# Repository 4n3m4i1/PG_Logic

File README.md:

# ProgrammaGull Logic
Small and open source FPGA development boards for all those still pecking for fries.  

## Hardware
Design files provided for KiCad 7.
  
### PGL Sandpiper
An education focused development platform, full of fun I/O and devices for users to learn the basics of real world FPGA development. The board centers around the Lattice iCE40-UP5k, which itself offers ample BRAM, PSRAM, 8 DSP Blocks, a PLL, and two internal oscillators.

### PGL E3
An iCE40-UP5k SG48 development board and associated programmer board.  
Designed to be embeddable and flexible enough for most projects!  
  
### PGL E6
A small embeddable Lattice iCE40-LP384 aimed at alleviating the overhead incurred when adding glue logic or general PL space into a project.

### PGL E6-NF
The same PGL E6 but with no flash, allowing smaller footprints when accompanied by some external bitstream source (MCU, external flash, other FPGA, etc..)

## Credits
Name: @slurpeecup

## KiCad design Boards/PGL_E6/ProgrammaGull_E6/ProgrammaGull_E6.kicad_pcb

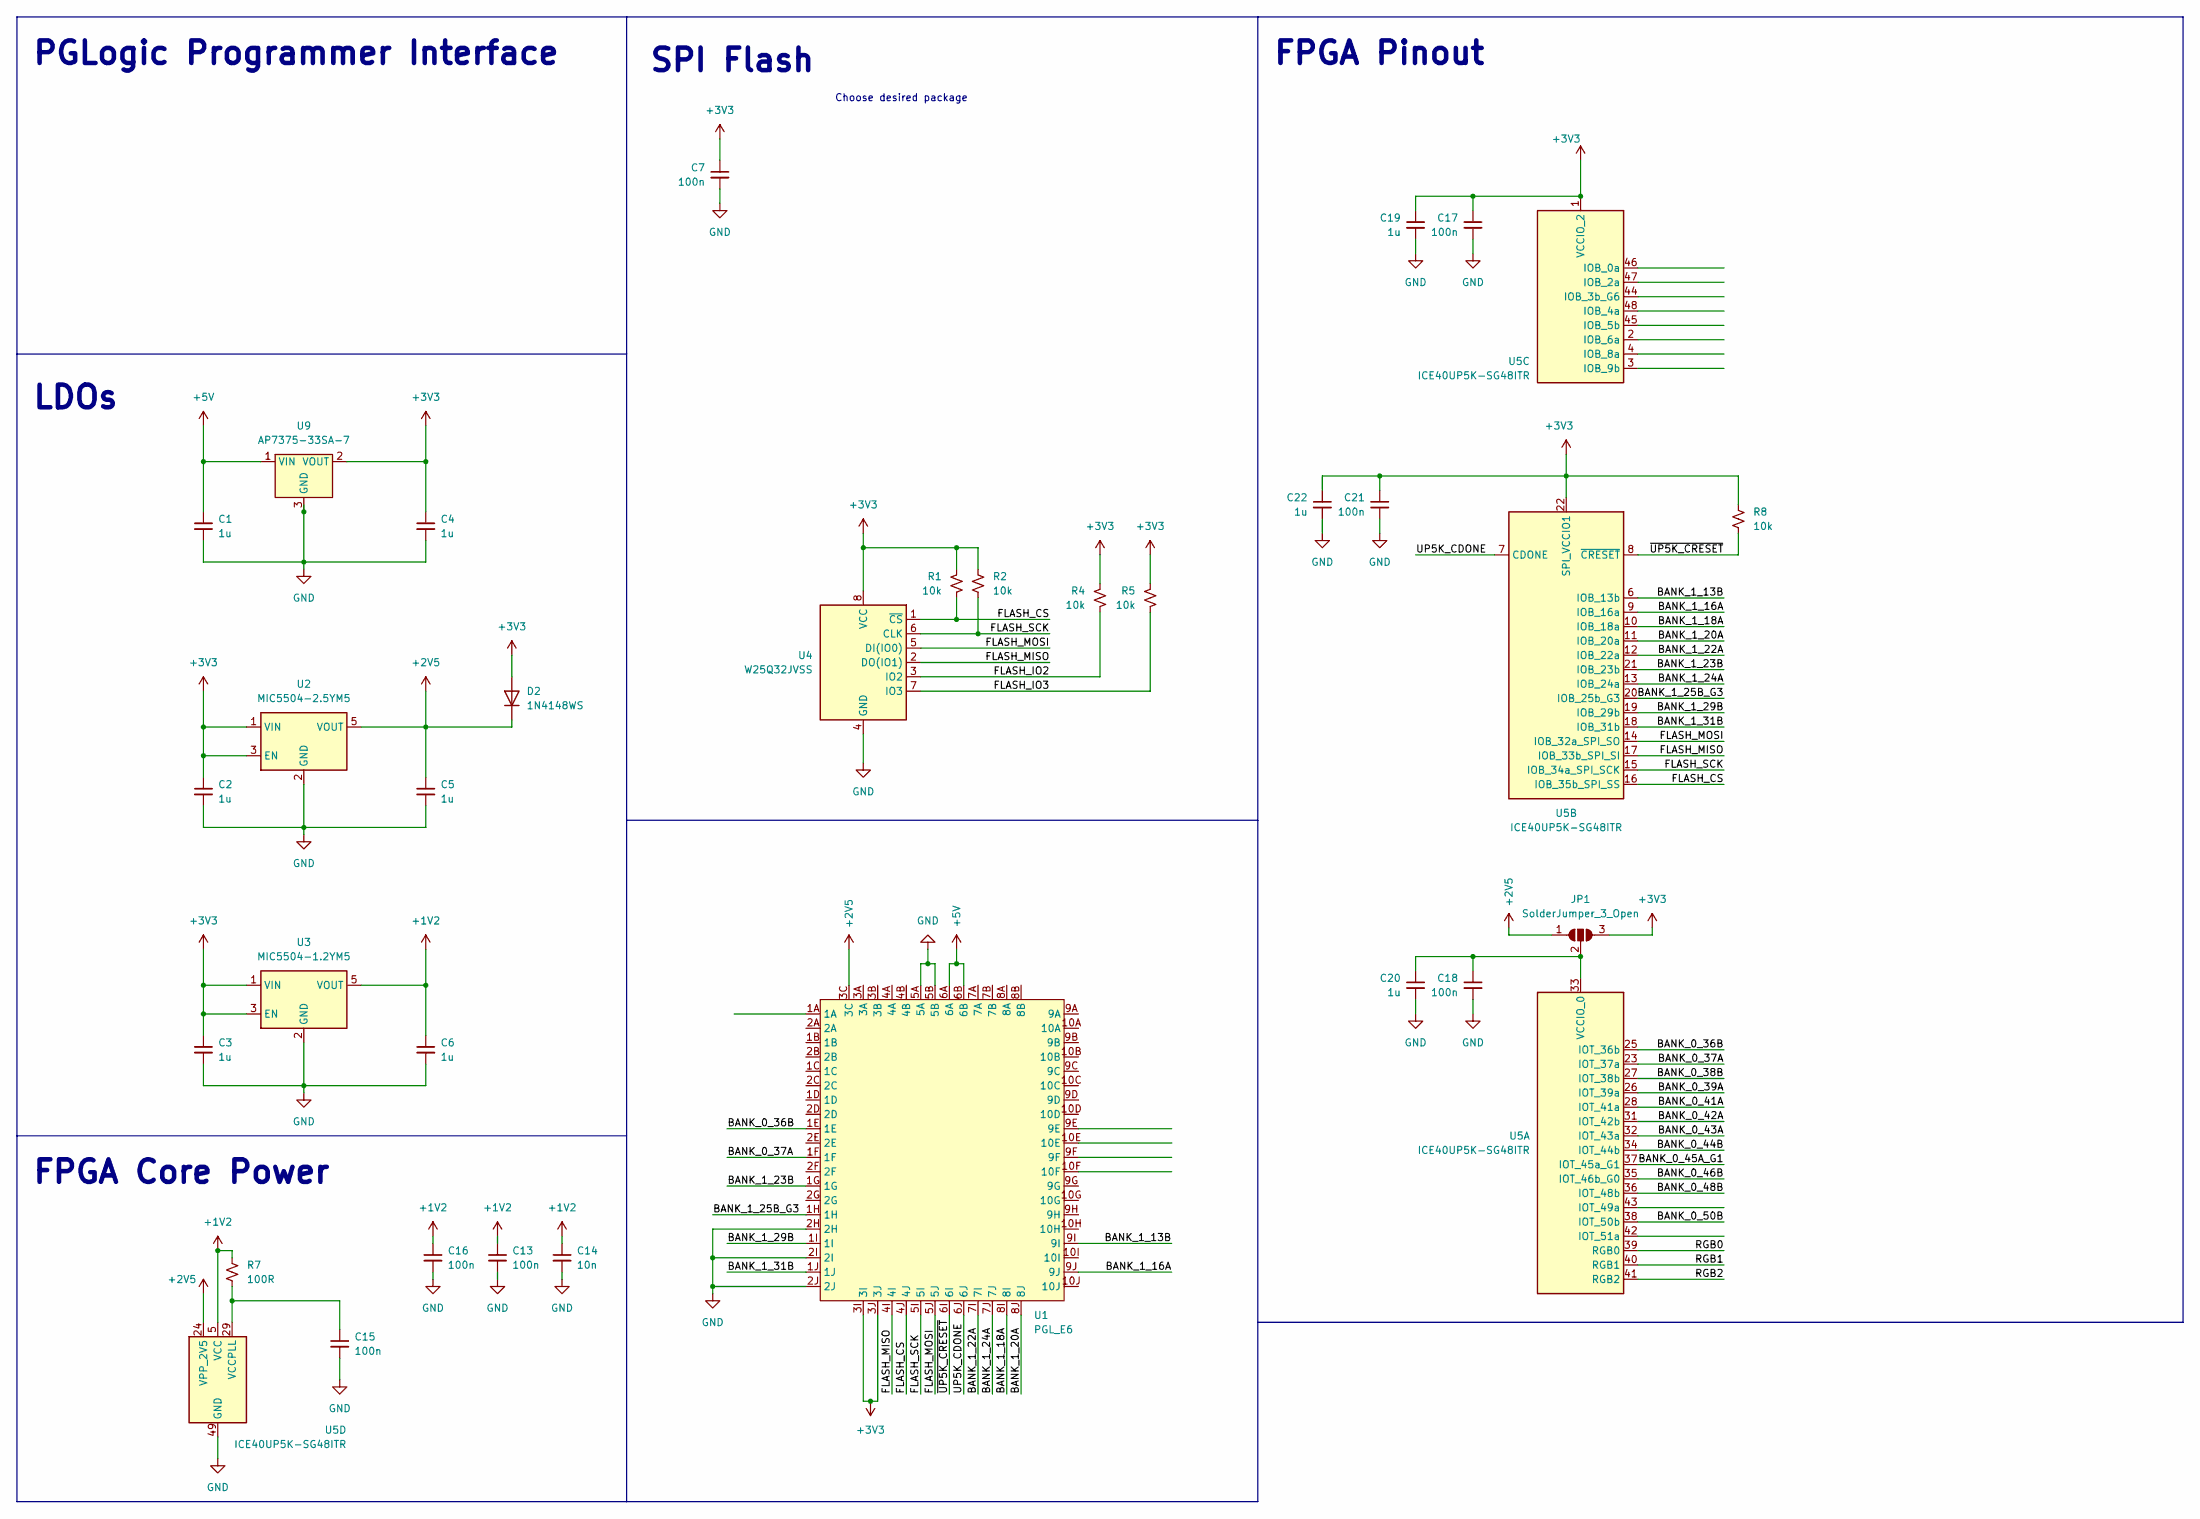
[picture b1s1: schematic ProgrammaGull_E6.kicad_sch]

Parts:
C1, C2, C3, C4, C5, C6, C19, C20, C22: 1u; C_0603_1608Metric
C7, C13, C15, C16, C17, C18, C21: 100n; C_0603_1608Metric
C14: 10n; C_0603_1608Metric
D2: 1N4148WS; D_SOD-323
JP1: SolderJumper_3_Open; SolderJumper-3_P2.0mm_Open_TrianglePad1.0x1.5mm
R1, R2, R4, R5, R8: 10k; R_0603_1608Metric
R7: 100R; R_0603_1608Metric
U1: PGL_E6
U2: MIC5504-2.5YM5; SOT-23-5
U3: MIC5504-1.2YM5; SOT-23-5
U4: W25Q32JVSS; SOIC-8_5.23x5.23mm_P1.27mm
U5: ICE40UP5K-SG48ITR; QFN-48-1EP_7x7mm_P0.5mm_EP5.6x5.6mm
U9: AP7375-33SA-7; SOT-23-3

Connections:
+1V2: C6.1, C13.1, C14.1, C16.1, R7.2, U3.5 (VOUT), U5.5 (VCC), U5.30 (VCC)
+2V5: C5.1, D2.1 (K), JP1.1 (A), U1.3C, U2.5 (VOUT), U5.24 (VPP_2V5)
+3V3: C2.1, C3.1, C4.1, C7.1, C17.1, C19.1, C21.1, C22.1, D2.2 (A), JP1.3 (B), R1.2, R2.2, R4.2, R5.2, R8.2, U1.3I, U1.3J, U2.1 (VIN), U2.3 (EN), U3.1 (VIN), U3.3 (EN), U4.8 (VCC), U5.1 (VCCIO_2), U5.22 (SPI_VCCIO1), U9.2 (VOUT)
+5V: C1.1, U1.6A, U1.6B, U9.1 (VIN)
/BANK_0_36B: U1.1E, U5.25 (IOT_36b)
/BANK_0_37A: U1.1F, U5.23 (IOT_37a)
/BANK_0_38B: U5.27 (IOT_38b)
/BANK_0_39A: U5.26 (IOT_39a)
/BANK_0_41A: U5.28 (IOT_41a)
/BANK_0_42A: U5.31 (IOT_42b)
/BANK_0_43A: U5.32 (IOT_43a)
/BANK_0_44B: U5.34 (IOT_44b)
/BANK_0_45A_G1: U5.37 (IOT_45a_G1)
/BANK_0_46B: U5.35 (IOT_46b_G0)
/BANK_0_48B: U5.36 (IOT_48b)
/BANK_0_50B: U5.38 (IOT_50b)
/BANK_1_13B: U1.9I, U5.6 (IOB_13b)
/BANK_1_16A: U1.9J, U5.9 (IOB_16a)
/BANK_1_18A: U1.8I, U5.10 (IOB_18a)
/BANK_1_20A: U1.8J, U5.11 (IOB_20a)
/BANK_1_22A: U1.7I, U5.12 (IOB_22a)
/BANK_1_23B: U1.1G, U5.21 (IOB_23b)
/BANK_1_24A: U1.7J, U5.13 (IOB_24a)
/BANK_1_25B_G3: U1.1H, U5.20 (IOB_25b_G3)
/BANK_1_29B: U1.1I, U5.19 (IOB_29b)
/BANK_1_31B: U1.1J, U5.18 (IOB_31b)
/FLASH_CS: R1.1, U1.4J, U4.1 (~CS), U5.16 (IOB_35b_SPI_SS)
/FLASH_IO2: R4.1, U4.3 (IO2)
/FLASH_IO3: R5.1, U4.7 (IO3)
/FLASH_MISO: U1.4I, U4.2 (DO(IO1)), U5.17 (IOB_33b_SPI_SI)
/FLASH_MOSI: U1.5J, U4.5 (DI(IO0)), U5.14 (IOB_32a_SPI_SO)
/FLASH_SCK: R2.1, U1.5I, U4.6 (CLK), U5.15 (IOB_34a_SPI_SCK)
/RGB0: U5.39 (RGB0)
/RGB1: U5.40 (RGB1)
/RGB2: U5.41 (RGB2)
/UP5K_CDONE: U1.6J, U5.7 (CDONE)
/~UP5K_CRESET: R8.1, U1.6I, U5.8 (~CRESET)
GND: C1.2, C2.2, C3.2, C4.2, C5.2, C6.2, C7.2, C13.2, C14.2, C15.2, C16.2, C17.2, C18.2, C19.2, C20.2, C21.2, C22.2, U1.2H, U1.2I, U1.2J, U1.5A, U1.5B, U2.2 (GND), U3.2 (GND), U4.4 (GND), U5.49 (GND), U9.3 (GND)
unnamed: C18.1, C20.1, JP1.2 (C), U5.33 (VCCIO_0)
unnamed: C15.1, R7.1, U5.29 (VCCPLL)

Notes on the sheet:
LDOs
SPI Flash
PGLogic Programmer Interface
FPGA Core Power
Choose desired package
FPGA Pinout

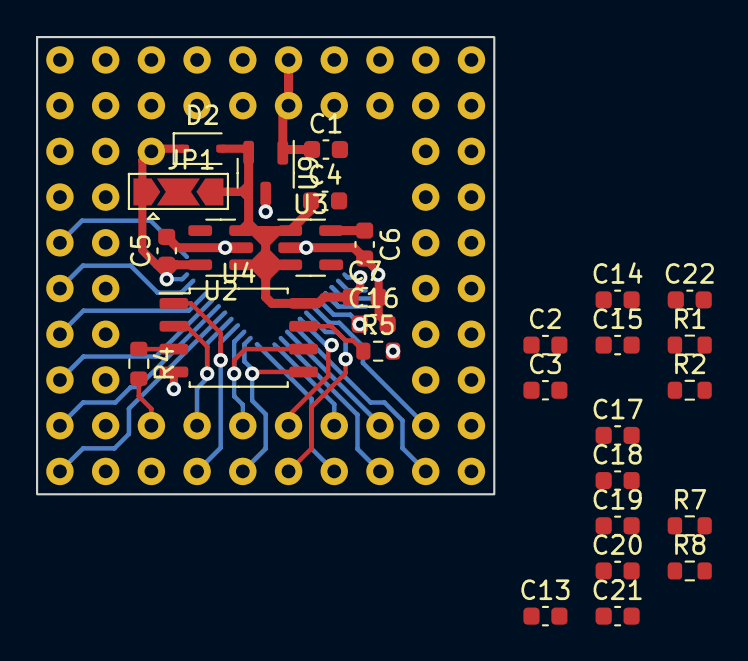
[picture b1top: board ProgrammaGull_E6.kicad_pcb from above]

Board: 4 copper layers, 25.4 x 25.4 mm, 31 parts (1 on the bottom side), 27 nets.

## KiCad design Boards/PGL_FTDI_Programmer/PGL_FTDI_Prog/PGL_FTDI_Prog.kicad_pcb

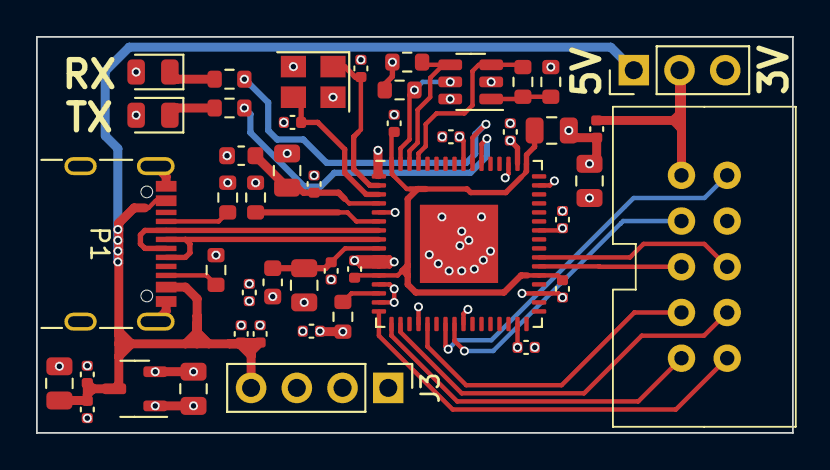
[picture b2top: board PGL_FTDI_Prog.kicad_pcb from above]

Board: 4 copper layers, 42.0 x 22.0 mm, 46 parts (0 on the bottom side), 31 nets.

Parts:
C1, C2, C9, C14, C26: 1u; C_0402_1005Metric
C4, C5, C6, C10, C12, C15, C16, C18, C19, C24, C25: 100n; C_0402_1005Metric
C7, C8, C11, C13, C17, C27: 4u7; C_0805_2012Metric
C22, C23: 33p C0G; C_0402_1005Metric
D2, D3: LED; LED_0805_2012Metric
FB1, FB2: FerriteBead_Small; L_0603_1608Metric
J1: Conn_01x03_Pin; PinHeader_1x03_P2.54mm_Vertical
J3: Conn_01x04; PinHeader_1x04_P2.54mm_Vertical
P1: USB_C_Plug_USB2.0; USB_C_Receptacle_GCT_USB4105-xx-A_16P_TopMnt_Horizontal
R1, R3, R5, R6: 10k; R_0603_1608Metric
R2: 2k2; R_0603_1608Metric
R4: 12k 1%; R_0603_1608Metric
R7, R8: 56k; R_0603_1608Metric
R11, R14: 330R; R_0603_1608Metric
U1: XC6206PxxxMR; SOT-23-3
U4: 93LCxxAxxOT; SOT-23-6
U5: FT2232HQ; QFN-64-1EP_9x9mm_P0.5mm_EP4.35x4.35mm
U7: PG_Logic_10_Pin_Tag_Connect_Programmer_Header; CH87102V200
Y1: 12.000 MHz, C9002; Crystal_SMD_3225-4Pin_3.2x2.5mm

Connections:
+1V8: C4.1, C7.1, C10.1, C15.1, U5.12 (VCORE), U5.37 (VCORE), U5.49 (VREGOUT), U5.64 (VCORE)
+3V3: C1.1, C16.1, C17.1, C18.1, C19.1, C25.1, C26.1, C27.1, D2.2 (A), D3.2 (A), FB1.2, FB2.2, J1.3, J3.2, R1.2, R3.2, R5.2, R6.2, U1.2 (VO), U4.6 (VCC), U5.20 (VCCIO), U5.31 (VCCIO), U5.42 (VCCIO), U5.50 (VREGIN), U5.56 (VCCIO)
+5V: C6.1, C9.1, C11.1, C14.1, C24.1, J1.1, J3.4, P1.A4 (VBUS), P1.A9 (VBUS), P1.B4 (VBUS), P1.B9 (VBUS), U1.3 (VI)
/EEPROM_SPI_CLK: R5.1, U4.4 (CLK), U5.62 (EECLK)
/EEPROM_SPI_CS: R1.1, U4.5 (CS), U5.63 (EECS)
/EEPROM_SPI_DI: R2.2, U4.3 (DI), U5.61 (EEDATA)
/EEPROM_SPI_DO: R2.1, R3.1, U4.1 (DO)
/FLASH_CS: U5.21 (ADBUS4), U7.7 (~F_CS)
/FLASH_MISO: U5.18 (ADBUS2), U7.8 (F_MISO)
/FLASH_MOSI: U5.17 (ADBUS1), U7.9 (F_MOSI)
/FLASH_SCK: U5.16 (ADBUS0), U7.10 (F_SCK)
/UP5K_CDONE: U5.23 (ADBUS6), U7.2 (CDONE)
/UP5K_CRESET: U5.24 (ADBUS7), U7.3 (~CRESET)
/UP5K_UART_RX: U5.38 (BDBUS0), U7.5 (UA_RX)
/UP5K_UART_TX: U5.39 (BDBUS1), U7.6 (UA_TX)
/USB_CC: P1.A5 (CC), R7.2
/USB_D+: P1.A6 (D+), U5.8 (DP)
/USB_D-: P1.A7 (D-), U5.7 (DM)
/USB_VCONN: P1.B5 (VCONN), R8.2
/XIN: C22.1, U5.2 (OSCI), Y1.1
/XOUT: C23.1, U5.3 (OSCO), Y1.3
GND: C1.2, C2.2, C4.2, C5.2, C6.2, C7.2, C8.2, C9.2, C10.2, C11.2, C12.2, C13.2, C14.2, C15.2, C16.2, C17.2, C18.2, C19.2, C22.2, C23.2, C24.2, C25.2, C26.2, C27.2, J3.1, J3.3, P1.A1 (GND), P1.A12 (GND), P1.B1 (GND), P1.B12 (GND), P1.S1 (SHIELD), R4.1, R7.1, R8.1, U1.1 (GND), U4.2 (GND), U5.1 (GND), U5.5 (GND), U5.10 (AGND), U5.11 (GND), U5.13 (TEST), U5.15 (GND), U5.25 (GND), U5.35 (GND), U5.47 (GND), U5.51 (GND), U5.65 (GND), U7.4 (GND), Y1.2, Y1.4
unnamed: D2.1 (K), R11.1
unnamed: D3.1 (K), R14.1
unnamed: C2.1, J1.2, U7.1 (5V)
unnamed: R14.2, U5.54 (BCBUS3)
unnamed: R11.2, U5.55 (BCBUS4)
unnamed: R4.2, U5.6 (REF)
unnamed: C5.1, C8.1, FB1.1, U5.4 (VPHY)
unnamed: C12.1, C13.1, FB2.1, U5.9 (VPLL)
unnamed: R6.1, U5.14 (~RESET)

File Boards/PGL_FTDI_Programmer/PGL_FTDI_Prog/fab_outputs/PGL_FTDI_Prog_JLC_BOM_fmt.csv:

Designator,Qty,Value,Footprint,LCSC Part Number
"C1, C2, C9, C14, C26",5,1u,Capacitor_SMD:C_0402_1005Metric,C52923
"C4, C5, C6, C10, C12, C15, C16, C18, C19, C24, C25",11,100n,Capacitor_SMD:C_0402_1005Metric,C307331
"C7, C8, C11, C13, C17, C27",6,4u7,Capacitor_SMD:C_0805_2012Metric,C1779
"C22, C23",2,33p C0G,Capacitor_SMD:C_0402_1005Metric,C1562
"D2, D3",2,LED,LED_SMD:LED_0805_2012Metric,C2297
"FB1, FB2",2,FerriteBead_Small,Inductor_SMD:L_0603_1608Metric,C1002
P1,1,USB_C_Plug_USB2.0,Connector_USB:USB_C_Receptacle_GCT_USB4105-xx-A_16P_TopMnt_Horizontal,C963413
"R1, R3, R5, R6",4,10k,Resistor_SMD:R_0603_1608Metric,C25804
R2,1,2k2,Resistor_SMD:R_0603_1608Metric,C4190
R4,1,12k 1%,Resistor_SMD:R_0603_1608Metric,C22790
"R7, R8",2,56k,Resistor_SMD:R_0603_1608Metric,C23206
"R11, R14",2,330R,Resistor_SMD:R_0603_1608Metric,C23151
U1,1,XC6206PxxxMR,Package_TO_SOT_SMD:SOT-23-3,C5446
U4,1,93LCxxAxxOT,Package_TO_SOT_SMD:SOT-23-6,C190271
U5,1,FT2232HQ,Package_DFN_QFN:QFN-64-1EP_9x9mm_P0.5mm_EP4.35x4.35mm,C193662
Y1,1,"12.000 MHz,  C9002 ",Crystal:Crystal_SMD_3225-4Pin_3.2x2.5mm,C9002
